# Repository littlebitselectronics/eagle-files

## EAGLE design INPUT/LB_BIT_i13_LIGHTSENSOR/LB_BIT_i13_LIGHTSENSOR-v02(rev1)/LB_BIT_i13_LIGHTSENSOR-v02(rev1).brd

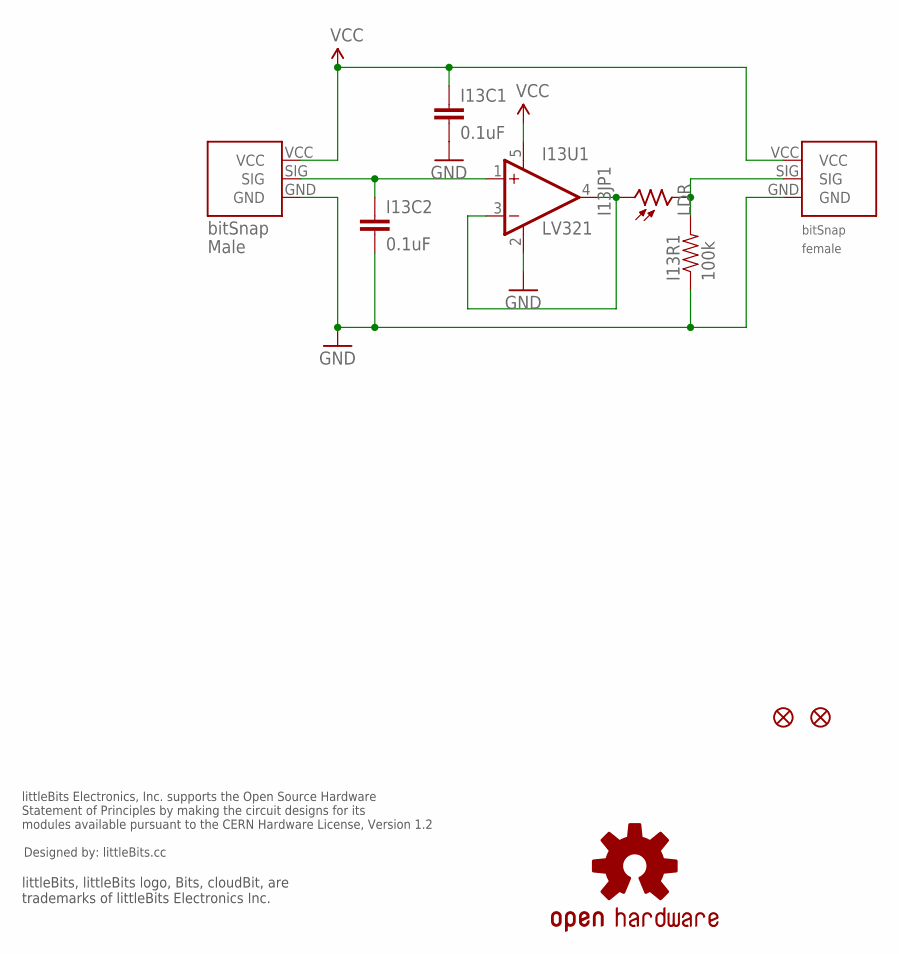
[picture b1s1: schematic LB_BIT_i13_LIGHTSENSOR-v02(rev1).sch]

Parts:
I13BSF: BITSNAP_FEMALE
I13BSM: BITSNAP_MALE
I13C1, I13C2: 0.1uF; 0603-CAP
I13FD1, I13FD2: FIDUCIAL1X2; FIDUCIAL-1X2
I13JP1: LDR; T0-46-A10XX
I13R1: 100k; 0603-RES
I13U1: LV321; SC70-5
U$1: OSHWCREDIT
U$19: OSHW-LOGOL; OSHW-LOGO-L

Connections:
GND: I13BSF.GND, I13BSM.GND, I13C1.2, I13C2.2, I13R1.1, I13U1.2 (V-)
unnamed: I13JP1.1, I13U1.3 (-IN), I13U1.4 (OUT)
PS: I13BSF.SIG, I13JP1.2, I13R1.2
SIG: I13BSM.SIG, I13C2.1, I13U1.1 (+IN)
VCC: I13BSF.VCC, I13BSM.VCC, I13C1.1, I13U1.5 (V+)

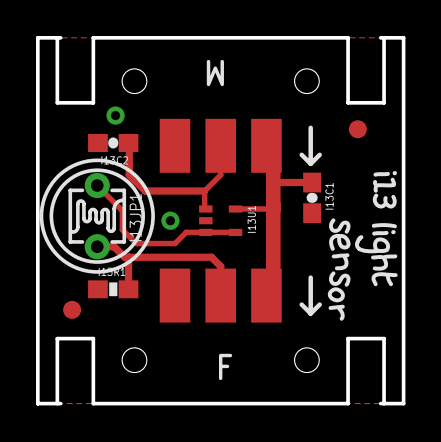
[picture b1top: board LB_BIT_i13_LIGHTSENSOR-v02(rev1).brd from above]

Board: 2 copper layers, 20.3 x 20.3 mm, 26 parts (0 on the bottom side), 5 nets.

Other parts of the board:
U$2, U$9: I
U$3: 1
U$5: 3
U$6: OSHW_FILLX150_NOTEXT
U$8: L
U$10: G
U$11: H
U$12: T
U$13, U$16: S
U$14: E
U$15: N
U$17: O
U$18: R

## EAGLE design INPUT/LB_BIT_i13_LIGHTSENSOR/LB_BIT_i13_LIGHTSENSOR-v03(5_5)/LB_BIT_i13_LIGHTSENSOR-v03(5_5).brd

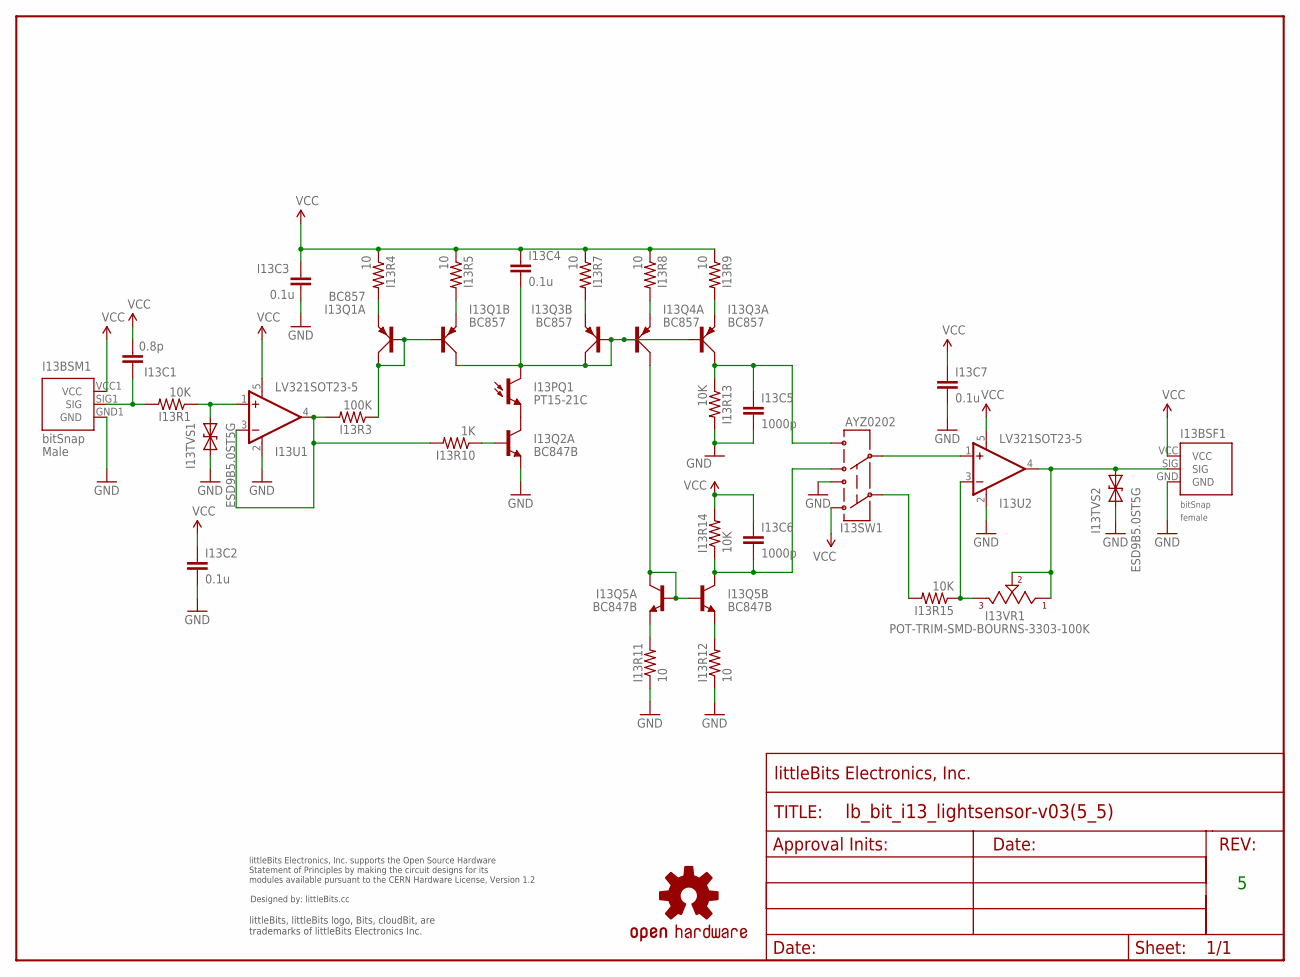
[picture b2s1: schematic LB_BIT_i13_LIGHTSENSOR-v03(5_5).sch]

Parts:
I13BSF1: BITSNAP_V03_FEMALE
I13BSM1: BITSNAP_V03_MALE
I13C1: 0.8p; CAP-0603
I13C2, I13C3, I13C4, I13C7: 0.1u; CAP-0603
I13C5, I13C6: 1000p; CAP-0603
I13PQ1: PT15-21C; PHOTOTRANS-1206
I13Q1, I13Q3, I13Q4: BC857; SOT-363_PHILLIPS
I13Q2, I13Q5: BC847B; SOT-363_PHILLIPS
I13R1, I13R13, I13R14, I13R15: 10K; RES-0603
I13R3: 100K; RES-0603
I13R4, I13R5, I13R7, I13R8, I13R9, I13R11, I13R12: 10; RES-0603
I13R10: 1K; RES-0603
I13SW1: AYZ0202
I13TVS1, I13TVS2: ESD9B5.0ST5G; SOD-923
I13U1, I13U2: LV321SOT23-5; SOT23-5
I13VR1: POT-TRIM-SMD-BOURNS-3303-100K; POT-TRIM-SMD-BOURNS-3303
U$1: OSHWCREDIT
U$2: OSHW-LOGOL; OSHW-LOGO-L
U$3: FRAME-LETTER-OHWOHW; FABDWG01-OHW

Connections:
GND: I13BSF1.GND, I13BSM1.GND1 (GND), I13C2.2, I13C3.2, I13C5.2, I13C7.2, I13Q2.1 (E), I13R11.1, I13R12.1, I13R13.2, I13SW1.3, I13TVS1.1 (A), I13TVS2.1 (A), I13U1.2 (V-), I13U2.2 (V-)
unnamed: I13C6.2, I13Q5.3 (C), I13R14.1, I13SW1.4
unnamed: I13Q5.1 (E), I13R11.2
unnamed: I13Q4.6 (C), I13Q5.2 (B), I13Q5.5 (B), I13Q5.6 (C)
unnamed: I13Q5.4 (E), I13R12.2
unnamed: I13BSM1.SIG1 (SIG), I13C1.1, I13R1.2
unnamed: I13R15.1, I13U2.3 (-IN), I13VR1.3
unnamed: I13BSF1.SIG, I13TVS2.2 (C), I13U2.4 (OUT), I13VR1.1, I13VR1.2
unnamed: I13R3.2, I13R10.2, I13U1.3 (-IN), I13U1.4 (OUT)
unnamed: I13Q1.2 (B), I13Q1.5 (B), I13Q1.6 (C), I13R3.1
unnamed: I13Q1.1 (E), I13R4.2
unnamed: I13Q1.4 (E), I13R5.2
unnamed: I13Q3.4 (E), I13R7.2
unnamed: I13C4.2, I13PQ1.C, I13Q1.3 (C), I13Q3.2 (B), I13Q3.3 (C), I13Q3.5 (B), I13Q4.2 (B)
unnamed: I13Q4.1 (E), I13R8.2
unnamed: I13Q3.1 (E), I13R9.2
unnamed: I13SW1.5, I13U2.1 (+IN)
unnamed: I13R15.2, I13SW1.2
unnamed: I13PQ1.E, I13Q2.6 (C)
unnamed: I13C5.1, I13Q3.6 (C), I13R13.1, I13SW1.6
unnamed: I13Q2.2 (B), I13R10.1
unnamed: I13R1.1, I13TVS1.2 (C), I13U1.1 (+IN)
VCC: I13BSF1.VCC, I13BSM1.VCC1 (VCC), I13C1.2, I13C2.1, I13C3.1, I13C4.1, I13C6.1, I13C7.1, I13R4.1, I13R5.1, I13R7.1, I13R8.1, I13R9.1, I13R14.2, I13SW1.1, I13U1.5 (V+), I13U2.5 (V+)

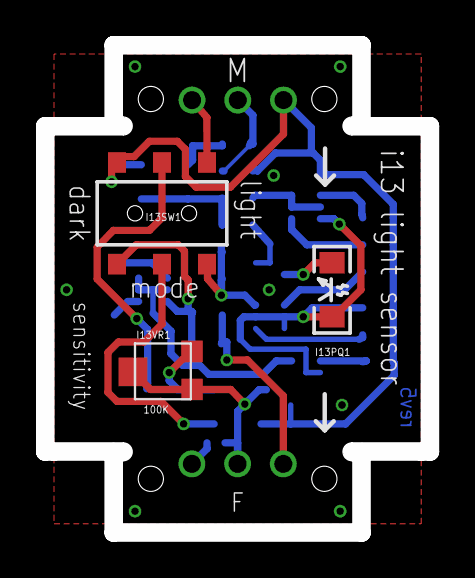
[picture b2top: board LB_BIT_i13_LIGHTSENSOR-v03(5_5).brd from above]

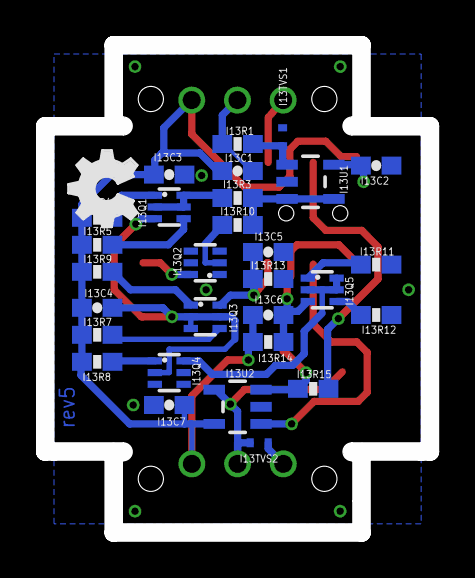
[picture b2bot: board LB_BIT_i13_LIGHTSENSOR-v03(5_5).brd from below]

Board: 2 copper layers, 21.4 x 27.1 mm, 38 parts (29 on the bottom side), 23 nets.

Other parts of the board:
U$6: OSHW_FILLX150_NOTEXT

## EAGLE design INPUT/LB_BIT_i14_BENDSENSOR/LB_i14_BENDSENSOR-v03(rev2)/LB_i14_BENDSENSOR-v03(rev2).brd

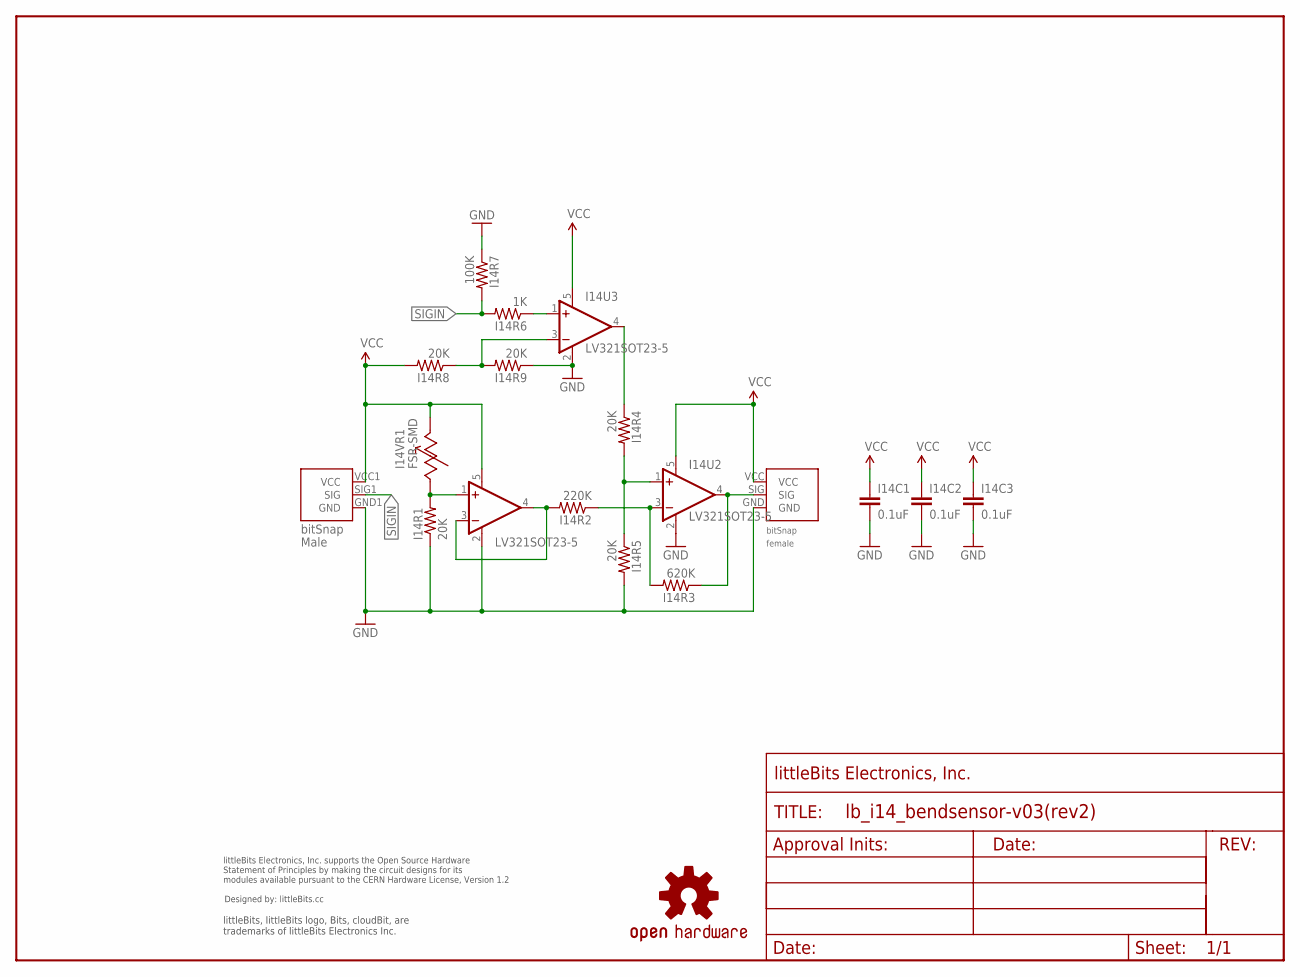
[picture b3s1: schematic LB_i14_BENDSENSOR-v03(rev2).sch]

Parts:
I14BSM: BITSNAP_V03_MALE
I14C1, I14C2, I14C3: 0.1uF; 0603-CAP
I14R1, I14R4, I14R5, I14R8, I14R9: 20K; 0603-RES
I14R2: 220K; 0603-RES
I14R3: 620K; 0603-RES
I14R6: 1K; 0603-RES
I14R7: 100K; 0603-RES
I14U1, I14U2, I14U3: LV321SOT23-5; SOT23-5
I14VR1: FSR-SMD
U$1: OSHW-LOGOL; OSHW-LOGO-L
U$2: FRAME-LETTER-OHWOHW; FABDWG01-OHW
U$3: OSHWCREDIT
U$4I14BSF: BITSNAP_V03_FEMALE

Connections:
GND: I14BSM.GND1 (GND), I14C1.2, I14C2.2, I14C3.2, I14R1.1, I14R5.2, I14R7.1, I14R9.1, I14U1.2 (V-), I14U2.2 (V-), I14U3.2 (V-), U$4I14BSF.GND
unnamed: I14R1.2, I14U1.1 (+IN), I14VR1.2 (A)
unnamed: I14R3.1, I14U2.4 (OUT), U$4I14BSF.SIG
unnamed: I14R2.1, I14R3.2, I14U2.3 (-IN)
unnamed: I14R4.2, I14R5.1, I14U2.1 (+IN)
unnamed: I14R4.1, I14U3.4 (OUT)
unnamed: I14R2.2, I14U1.3 (-IN), I14U1.4 (OUT)
unnamed: I14R8.1, I14R9.2, I14U3.3 (-IN)
unnamed: I14R6.1, I14U3.1 (+IN)
SIGIN: I14BSM.SIG1 (SIG), I14R6.2, I14R7.2
VCC: I14BSM.VCC1 (VCC), I14C1.1, I14C2.1, I14C3.1, I14R8.2, I14U1.5 (V+), I14U2.5 (V+), I14U3.5 (V+), I14VR1.1, U$4I14BSF.VCC

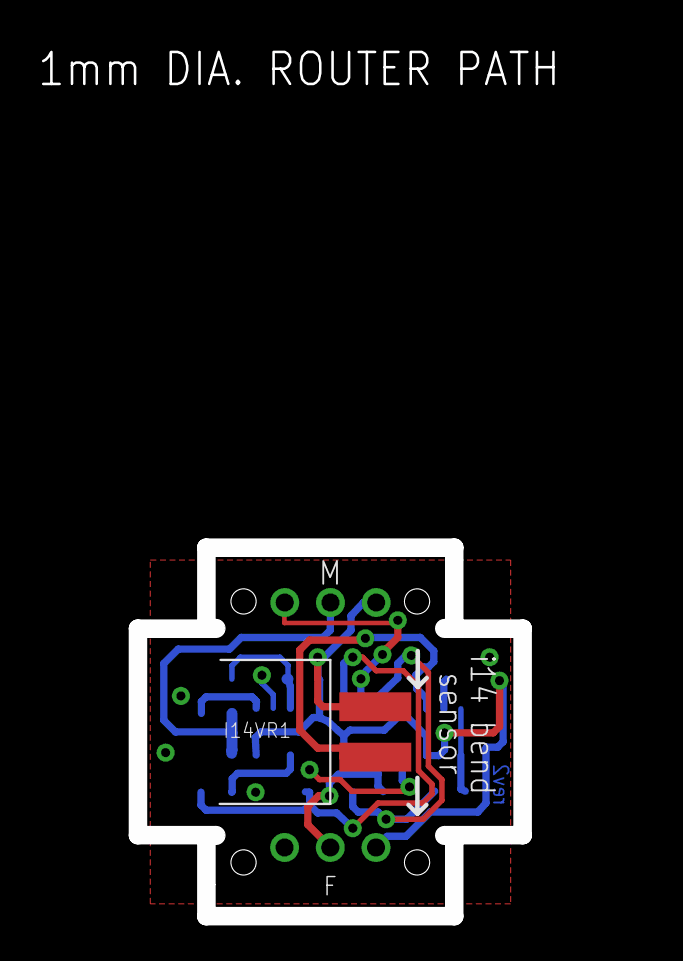
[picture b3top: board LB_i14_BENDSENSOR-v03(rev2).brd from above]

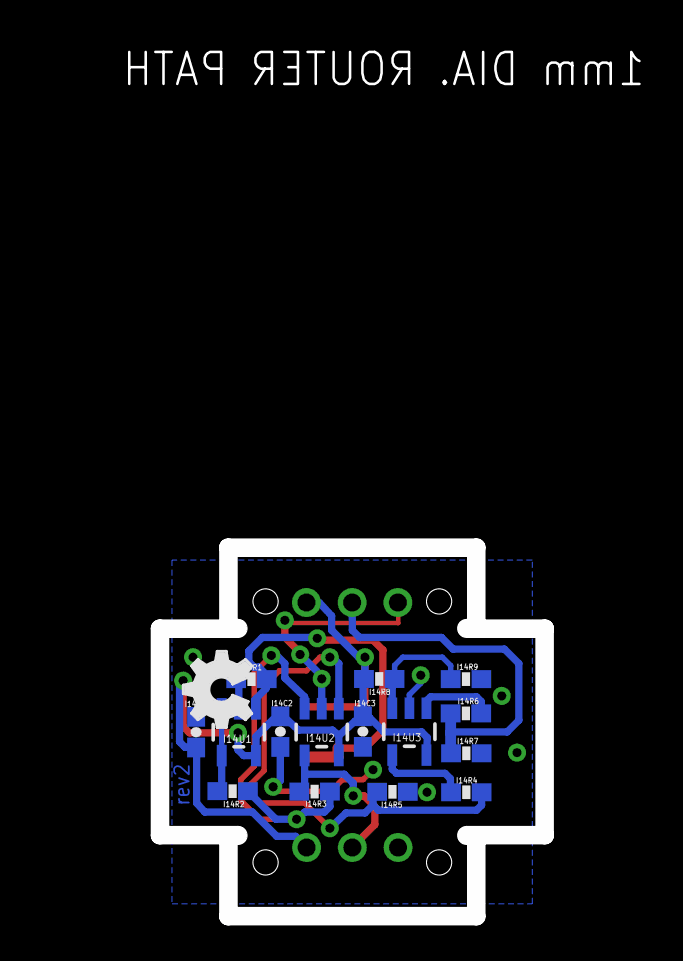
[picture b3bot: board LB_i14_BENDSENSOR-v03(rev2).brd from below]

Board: 2 copper layers, 21.4 x 20.5 mm, 22 parts (15 on the bottom side), 11 nets.

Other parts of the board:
U$7: OSHW_FILLX150_NOTEXT

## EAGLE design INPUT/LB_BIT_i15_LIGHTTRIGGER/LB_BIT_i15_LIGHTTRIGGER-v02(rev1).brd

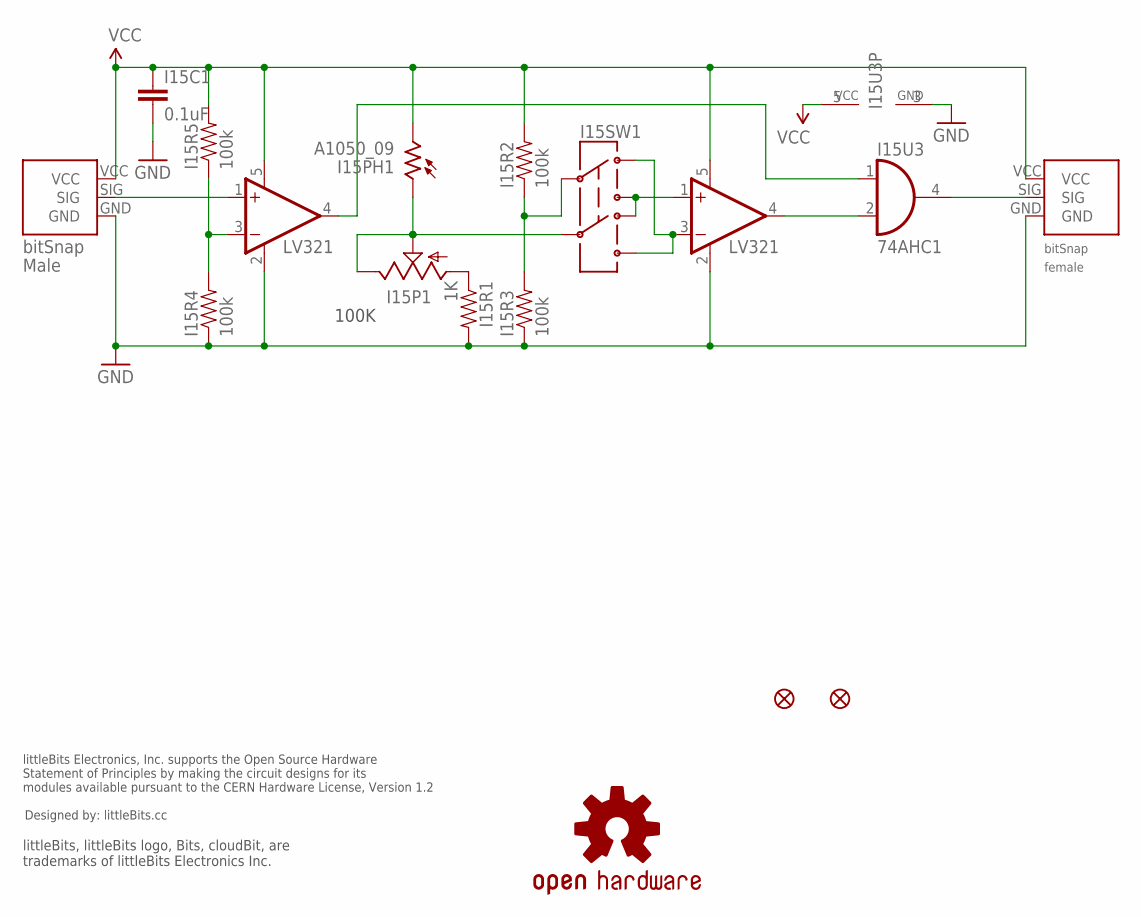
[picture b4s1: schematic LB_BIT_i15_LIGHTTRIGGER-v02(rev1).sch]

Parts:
I15BSF: BITSNAP_FEMALE
I15BSM: BITSNAP_MALE
I15C1: 0.1uF; 0603-CAP
I15FD1, I15FD2: FIDUCIAL1X2; FIDUCIAL-1X2
I15P1: POT-TRIM-SMD-BOURNS-3303
I15PH1: A1050_09; T0-46-A10XX
I15R1: 1K; 0603-RES
I15R2, I15R3, I15R4, I15R5: 100k; 0603-RES
I15SW1: SWITCH-DPDTSMD; AYZ0202
I15U1, I15U2: LV321; SC70
I15U3: 74AHC1; SOT23-5
U$6: OSHW-LOGOL; OSHW-LOGO-L
U$7: OSHWCREDIT

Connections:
GND: I15BSF.GND, I15BSM.GND, I15C1.2, I15R1.2, I15R3.1, I15R4.1, I15U1.2 (V-), I15U2.2 (V-), I15U3.3 (GND)
unnamed: I15SW1.3, I15SW1.4, I15U2.1 (+IN)
unnamed: I15SW1.1, I15SW1.6, I15U2.3 (-IN)
unnamed: I15P1.1 (A), I15R1.1
unnamed: I15U2.4 (OUT), I15U3.2 (I1)
unnamed: I15BSF.SIG, I15U3.4 (O)
unnamed: I15R2.1, I15R3.2, I15SW1.2
unnamed: I15P1.2 (S), I15P1.3 (E), I15PH1.1, I15SW1.5
unnamed: I15BSM.SIG, I15U1.1 (+IN)
unnamed: I15R4.2, I15R5.1, I15U1.3 (-IN)
unnamed: I15U1.4 (OUT), I15U3.1 (I0)
VCC: I15BSF.VCC, I15BSM.VCC, I15C1.1, I15PH1.2, I15R2.2, I15R5.2, I15U1.5 (V+), I15U2.5 (V+), I15U3.5 (VCC)

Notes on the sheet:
100K

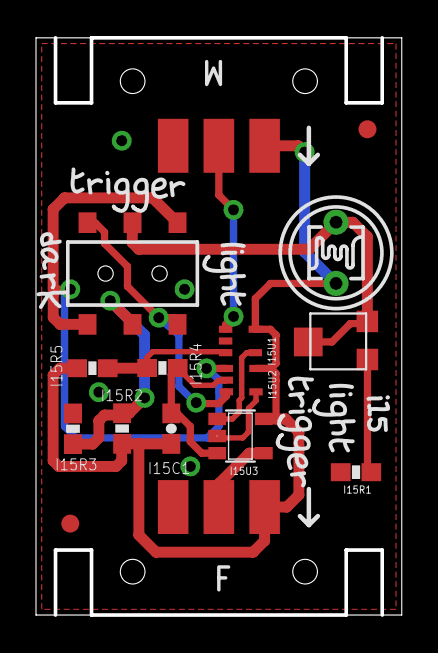
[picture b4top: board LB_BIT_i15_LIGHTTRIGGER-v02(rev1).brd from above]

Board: 2 copper layers, 20.3 x 32.1 mm, 50 parts (0 on the bottom side), 12 nets.

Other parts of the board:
U$1, U$18, U$43, U$44: T
U$2, U$11, U$20, U$45, U$50: R
U$3, U$15, U$36, U$40, U$46: I
U$4, U$13, U$16, U$41, U$47, U$48: G
U$5: D
U$8: OSHW_FILLX150_NOTEXT
U$10: A
U$12: K
U$14, U$39: L
U$17, U$42: H
U$19, U$49: E
U$37: 1
U$38: 5

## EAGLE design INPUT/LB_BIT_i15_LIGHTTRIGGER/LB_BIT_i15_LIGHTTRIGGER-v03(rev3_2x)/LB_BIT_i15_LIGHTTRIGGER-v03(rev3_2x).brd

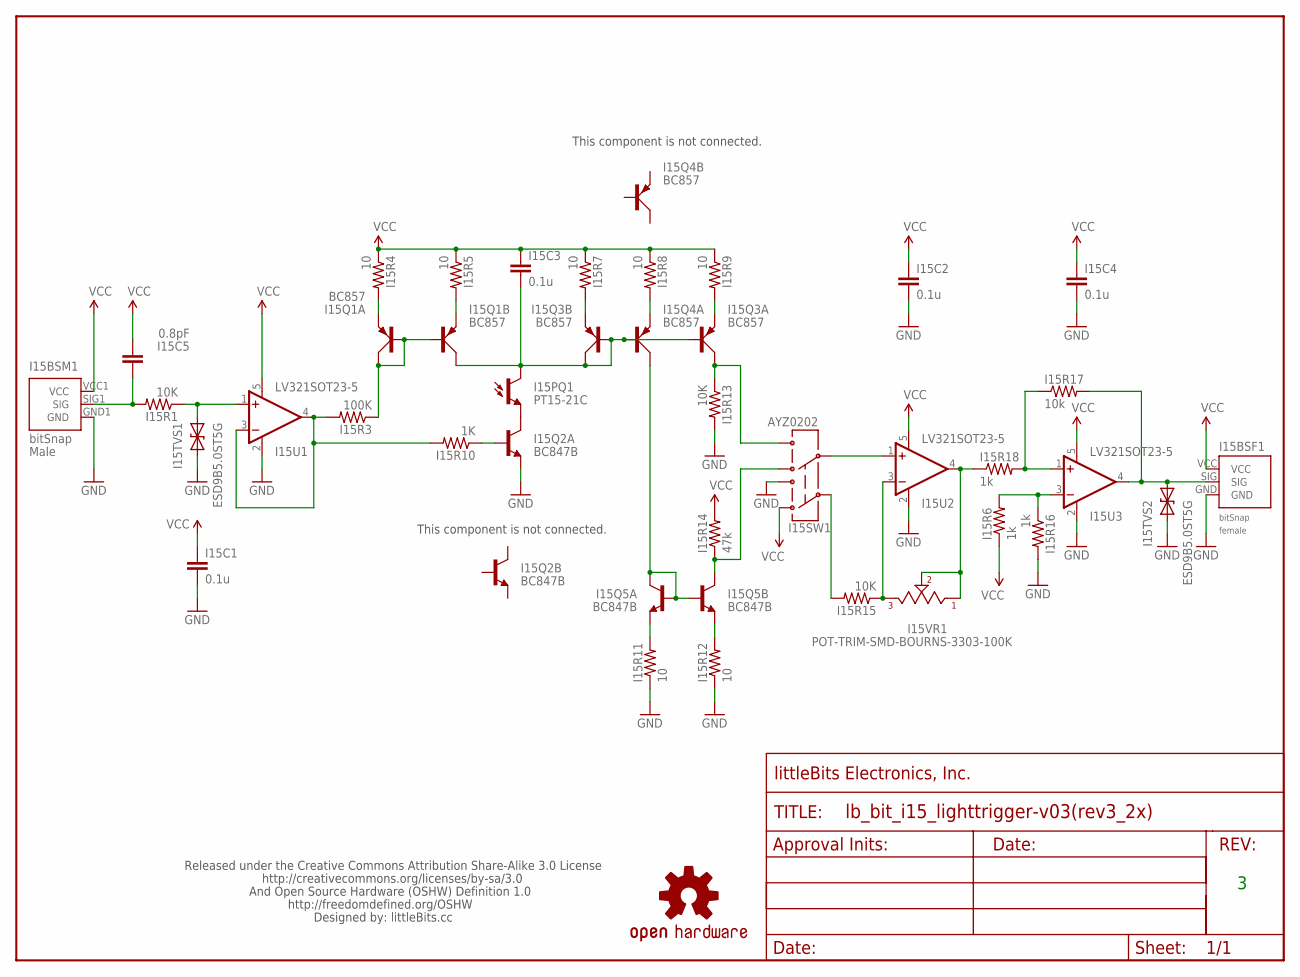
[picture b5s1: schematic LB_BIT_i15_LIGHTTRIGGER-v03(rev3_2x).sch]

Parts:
FRAME1: FRAME-LETTER-OHWOHW; FABDWG01-OHW
I15BSF1: BITSNAP_V03_FEMALE
I15BSM1: BITSNAP_V03_MALE
I15C1, I15C2, I15C3, I15C4: 0.1u; CAP-0603
I15C5: 0.8pF; CAP-0603
I15PQ1: PT15-21C; PHOTOTRANS-1206
I15Q1, I15Q3, I15Q4: BC857; SOT-363_PHILLIPS
I15Q2, I15Q5: BC847B; SOT-363_PHILLIPS
I15R1, I15R13, I15R15: 10K; RES-0603
I15R3: 100K; RES-0603
I15R4, I15R5, I15R7, I15R8, I15R9, I15R11, I15R12: 10; RES-0603
I15R6, I15R16, I15R18: 1k; RES-0603
I15R10: 1K; RES-0603
I15R14: 47k; RES-0603
I15R17: 10k; RES-0603
I15SW1: AYZ0202
I15TVS1, I15TVS2: ESD9B5.0ST5G; SOD-923
I15U1, I15U2, I15U3: LV321SOT23-5; SOT23-5
I15VR1: POT-TRIM-SMD-BOURNS-3303-100K; POT-TRIM-SMD-BOURNS-3303
U$1: OSHWCREDIT
U$2: OSHW-LOGOL; OSHW-LOGO-L

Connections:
GND: I15BSF1.GND, I15BSM1.GND1 (GND), I15C1.2, I15C2.2, I15C4.2, I15Q2.1 (E), I15R11.1, I15R12.1, I15R13.2, I15R16.2, I15SW1.3, I15TVS1.1 (A), I15TVS2.1 (A), I15U1.2 (V-), I15U2.2 (V-), I15U3.2 (V-)
unnamed: I15Q5.3 (C), I15R14.1, I15SW1.4
unnamed: I15Q5.1 (E), I15R11.2
unnamed: I15Q4.6 (C), I15Q5.2 (B), I15Q5.5 (B), I15Q5.6 (C)
unnamed: I15Q5.4 (E), I15R12.2
unnamed: I15BSM1.SIG1 (SIG), I15C5.1, I15R1.2
unnamed: I15R15.1, I15U2.3 (-IN), I15VR1.3
unnamed: I15R18.1, I15U2.4 (OUT), I15VR1.1, I15VR1.2
unnamed: I15R3.2, I15R10.2, I15U1.3 (-IN), I15U1.4 (OUT)
unnamed: I15Q1.2 (B), I15Q1.5 (B), I15Q1.6 (C), I15R3.1
unnamed: I15Q1.1 (E), I15R4.2
unnamed: I15Q1.4 (E), I15R5.2
unnamed: I15Q3.4 (E), I15R7.2
unnamed: I15C3.2, I15PQ1.C, I15Q1.3 (C), I15Q3.2 (B), I15Q3.3 (C), I15Q3.5 (B), I15Q4.2 (B)
unnamed: I15Q4.1 (E), I15R8.2
unnamed: I15Q3.1 (E), I15R9.2
unnamed: I15SW1.5, I15U2.1 (+IN)
unnamed: I15R15.2, I15SW1.2
unnamed: I15PQ1.E, I15Q2.6 (C)
unnamed: I15Q3.6 (C), I15R13.1, I15SW1.6
unnamed: I15Q2.2 (B), I15R10.1
unnamed: I15R1.1, I15TVS1.2 (C), I15U1.1 (+IN)
unnamed: I15R6.2, I15R16.1, I15U3.3 (-IN)
unnamed: I15R17.1, I15R18.2, I15U3.1 (+IN)
unnamed: I15BSF1.SIG, I15R17.2, I15TVS2.2 (C), I15U3.4 (OUT)
VCC: I15BSF1.VCC, I15BSM1.VCC1 (VCC), I15C1.1, I15C2.1, I15C3.1, I15C4.1, I15C5.2, I15R4.1, I15R5.1, I15R6.1, I15R7.1, I15R8.1, I15R9.1, I15R14.2, I15SW1.1, I15U1.5 (V+), I15U2.5 (V+), I15U3.5 (V+)

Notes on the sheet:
This component is not connected.

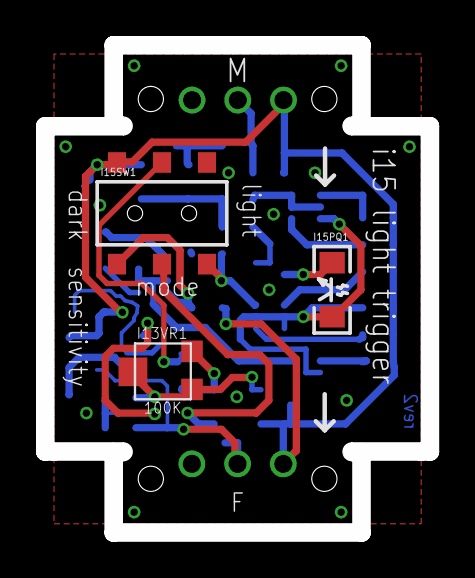
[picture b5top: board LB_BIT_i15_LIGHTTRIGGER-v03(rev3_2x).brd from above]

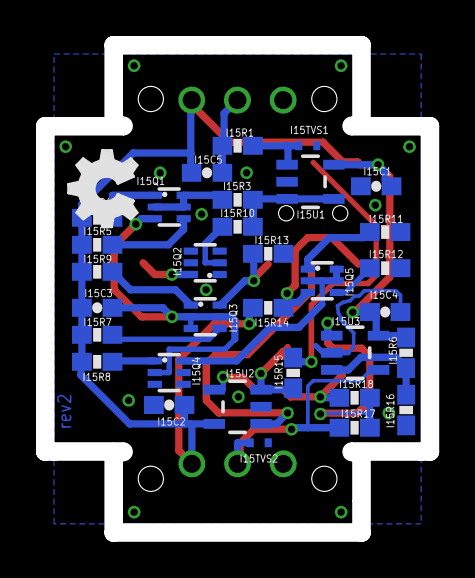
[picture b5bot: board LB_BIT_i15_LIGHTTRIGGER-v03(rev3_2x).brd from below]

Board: 2 copper layers, 21.4 x 27.1 mm, 41 parts (32 on the bottom side), 26 nets.

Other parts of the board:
U$6: OSHW_FILLX150_NOTEXT

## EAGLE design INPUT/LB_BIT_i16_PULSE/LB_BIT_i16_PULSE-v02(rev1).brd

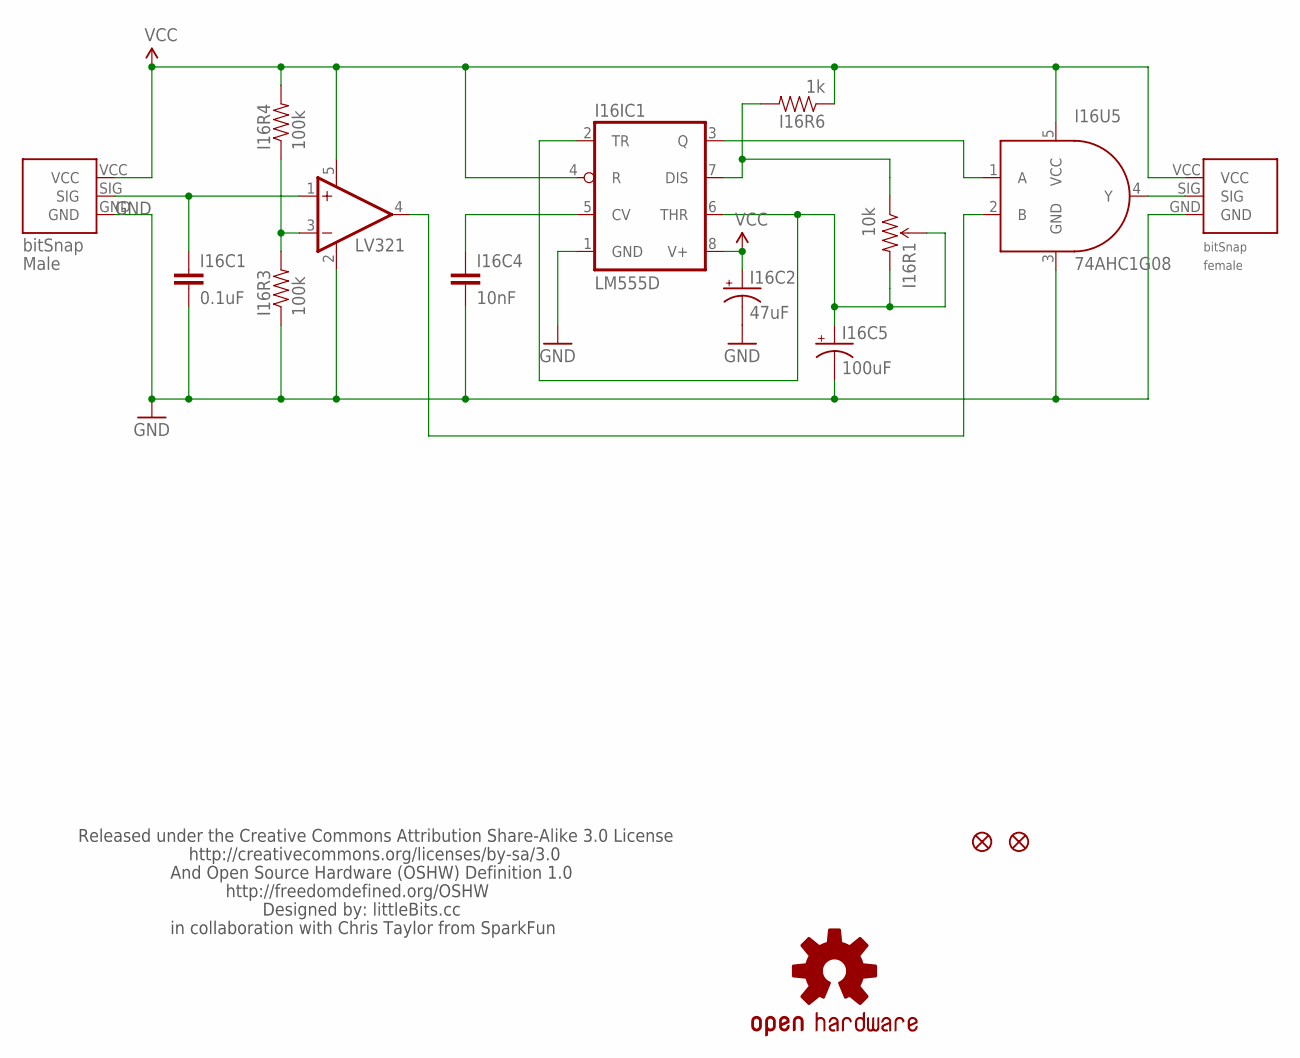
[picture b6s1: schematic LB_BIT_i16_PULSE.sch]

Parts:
I16BSF: BITSNAP_FEMALE
I16BSM: BITSNAP_MALE
I16C1: 0.1uF; 0603-CAP
I16C2: 47uF; EIA3528
I16C4: 10nF; 0603-CAP
I16C5: 100uF; PANASONIC_C
I16IC1: LM555D; SO08
I16R1: 10k; TRIMPOT-3MM
I16R3, I16R4: 100k; 0603-RES
I16R6: 1k; 0603-RES
I16U1: LV321; SC70
I16U5: 74AHC1G08; SOT23-5
JP1, JP2: FIDUCIAL1X2.5; FIDUCIAL-1X2.5
U$1: LB_CREDITS; OSHWCREDIT
U$5: OSHW-LOGOL; OSHW-LOGO-L

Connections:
GND: I16BSF.GND, I16BSM.GND, I16C1.2, I16C2.C (-), I16C4.2, I16C5.-, I16IC1.1 (GND), I16R3.1, I16U1.2 (V-), I16U5.3 (GND)
unnamed: I16IC1.3 (Q), I16U5.1 (A)
unnamed: I16R3.2, I16R4.1, I16U1.3 (-IN)
unnamed: I16U1.4 (OUT), I16U5.2 (B)
unnamed: I16C4.1, I16IC1.5 (CV)
unnamed: I16IC1.7 (DIS), I16R1.1 (CCW), I16R6.2
unnamed: I16C5.+, I16IC1.2 (TR), I16IC1.6 (THR), I16R1.2 (WIPER), I16R1.3 (CW)
PUL: I16BSF.SIG, I16U5.4 (Y)
SIG: I16BSM.SIG, I16C1.1, I16U1.1 (+IN)
VCC: I16BSF.VCC, I16BSM.VCC, I16C2.A (+), I16IC1.4 (R), I16IC1.8 (V+), I16R4.2, I16R6.1, I16U1.5 (V+), I16U5.5 (VCC)

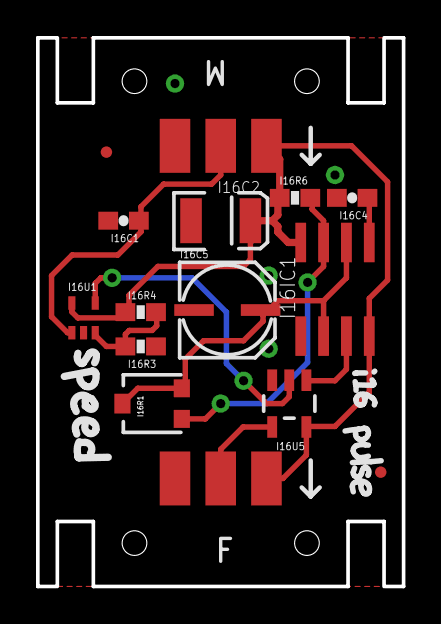
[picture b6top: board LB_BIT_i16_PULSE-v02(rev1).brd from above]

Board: 2 copper layers, 20.3 x 30.5 mm, 18 parts (0 on the bottom side), 10 nets.

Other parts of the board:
U$4: OSHW_FILLX150_NOTEXT

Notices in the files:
parts and their libraries:
LITTLEBITS: modules available pursuant to the CERN Hardware License,
Version 1.2
SparkFun_NEW: Licensing: CC v3.0 Share-Alike You are welcome to use this library for commercial purposes.
LITTLEBITS: modules available pursuant to the CERN Hardware License, Version 1.2
